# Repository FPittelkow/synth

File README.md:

# synth

The circuit is based on the [Totoro-Synth by SyntherJack](https://syntherjack.net/totoro-1-ic-simple-synth/)

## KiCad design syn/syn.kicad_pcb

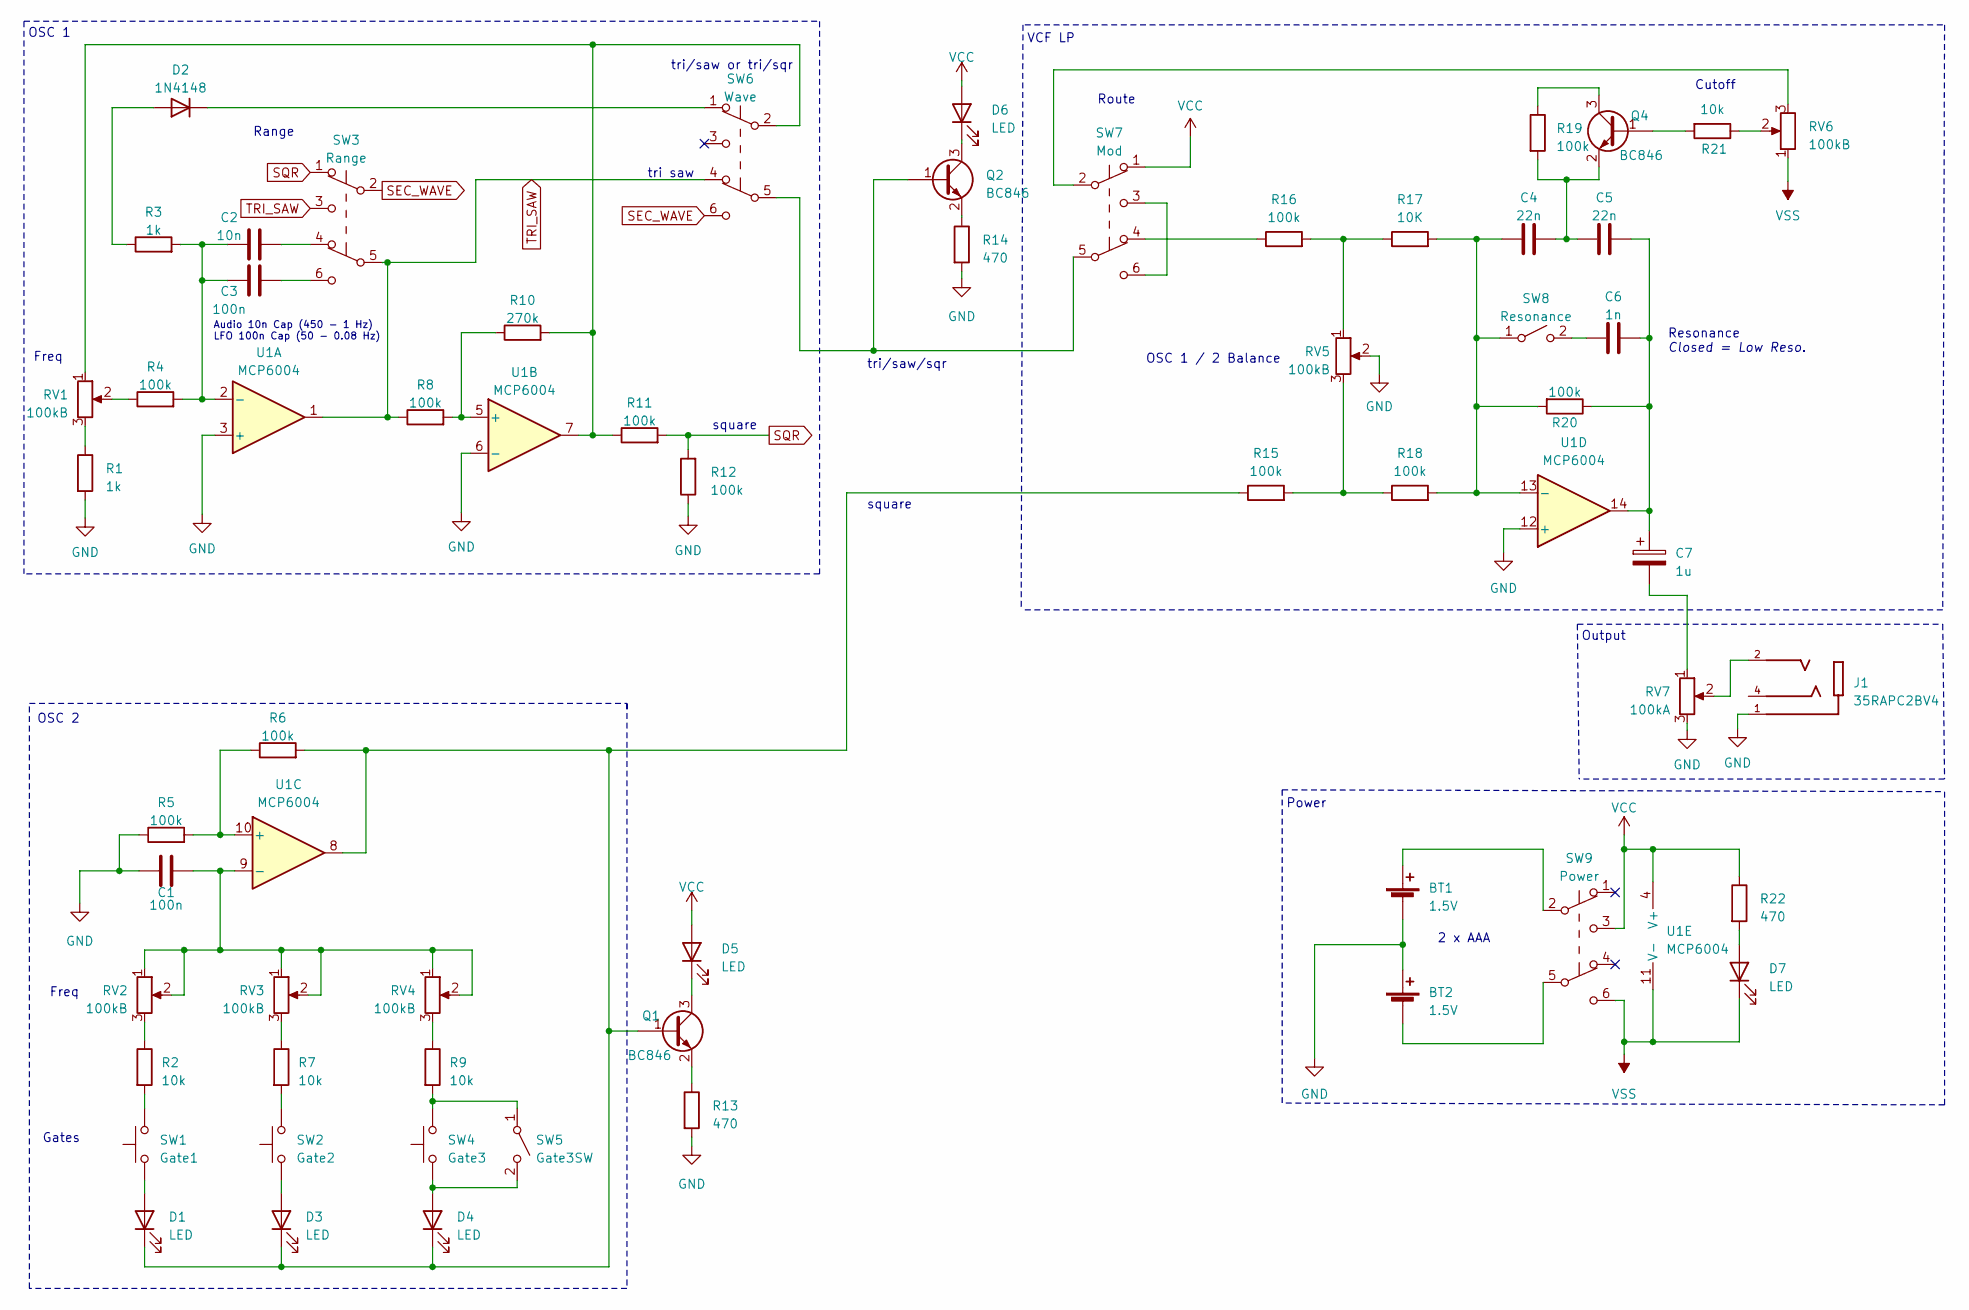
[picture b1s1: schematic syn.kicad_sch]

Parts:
BT1, BT2: 1.5V; BatteryHolder_Keystone_2466_1xAAA
C1, C3: 100n; C_0805_2012Metric_Pad1.18x1.45mm_HandSolder
C2: 10n; C_0805_2012Metric_Pad1.18x1.45mm_HandSolder
C4, C5: 22n; C_0805_2012Metric_Pad1.18x1.45mm_HandSolder
C6: 1n; C_0805_2012Metric_Pad1.18x1.45mm_HandSolder
C7: 1u; C_0805_2012Metric_Pad1.18x1.45mm_HandSolder
D1, D3, D4, D5, D6, D7: LED; LED_D3.0mm
D2: 1N4148; D_DO-35_SOD27_P7.62mm_Horizontal
J1: 35RAPC2BV4; SWITCHCRAFT_35RAPC2BV4; PARTREV G
Q1, Q2, Q4: BC846; SOT-23
R1, R3: 1k; R_0805_2012Metric_Pad1.20x1.40mm_HandSolder
R2, R7, R9, R21: 10k; R_0805_2012Metric_Pad1.20x1.40mm_HandSolder
R4, R5, R6, R8, R11, R12, R15, R16, R18, R19, R20: 100k; R_0805_2012Metric_Pad1.20x1.40mm_HandSolder
R10: 270k; R_0805_2012Metric_Pad1.20x1.40mm_HandSolder
R13, R14, R22: 470; R_0805_2012Metric_Pad1.20x1.40mm_HandSolder
R17: 10K; R_0805_2012Metric_Pad1.20x1.40mm_HandSolder
RV1, RV2, RV3, RV4, RV5, RV6: 100kB; Potentiometer_Bourns_PTV09A-1_Single_Vertical
RV7: 100kA; Potentiometer_Bourns_PTV09A-1_Single_Vertical
SW1: Gate1; SW_PUSH_6mm_H9.5mm
SW2: Gate2; SW_PUSH_6mm_H9.5mm
SW3: Range; SW_NKK_G1xJP
SW4: Gate3; SW_PUSH_6mm_H9.5mm
SW5: Gate3SW; SW_NKK_G1xJP
SW6: Wave; SW_NKK_G1xJP
SW7: Mod; SW_NKK_G1xJP
SW8: Resonance; SW_NKK_G1xJP
SW9: Power; SW_NKK_G1xJP
U1: MCP6004; DIP-14_W7.62mm

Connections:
GND: BT1.2 (-), BT2.1 (+), C1.1, J1.1, R1.2, R5.1, R12.1, R13.2, R14.2, RV5.2, RV7.3, U1.3 (+), U1.6 (-), U1.12 (+)
unnamed: BT1.1 (+), SW9.2 (B)
unnamed: BT2.2 (-), SW9.5 (B)
unnamed: C1.2, RV2.1, RV2.2, RV3.1, RV3.2, RV4.1, RV4.2, U1.9 (-)
unnamed: C2.1, C3.1, R3.2, R4.2, U1.2 (-)
unnamed: C2.2, SW3.4 (A)
unnamed: C3.2, SW3.6 (C)
unnamed: C4.1, R17.2, R18.2, R20.2, SW8.1 (A), U1.13 (-)
unnamed: C4.2, C5.1, Q4.2 (E), R19.2
unnamed: C5.2, C6.2, C7.1, R20.1, U1.14
unnamed: C6.1, SW8.2 (B)
unnamed: C7.2, RV7.1
unnamed: D1.1 (K), D3.1 (K), D4.1 (K), Q1.1 (B), R6.2, R15.1, U1.8
unnamed: D1.2 (A), SW1.1
unnamed: D2.1 (K), SW6.1 (A)
unnamed: D2.2 (A), R3.1
unnamed: D3.2 (A), SW2.1
unnamed: D4.2 (A), SW4.1, SW5.2 (B)
unnamed: D5.1 (K), Q1.3 (C)
unnamed: D6.1 (K), Q2.3 (C)
unnamed: D7.2 (A), R22.2
unnamed: J1.2, RV7.2
unnamed: Q1.2 (E), R13.1
unnamed: Q2.1 (B), SW6.5 (B), SW7.5 (B)
unnamed: Q2.2 (E), R14.1
unnamed: Q4.1 (B), R21.2
unnamed: Q4.3 (C), R19.1
unnamed: R1.1, RV1.3
unnamed: R2.1, RV2.3
unnamed: R2.2, SW1.2
unnamed: R4.1, RV1.2
unnamed: R5.2, R6.1, U1.10 (+)
unnamed: R7.1, RV3.3
unnamed: R7.2, SW2.2
unnamed: R9.1, RV4.3
unnamed: R9.2, SW4.2, SW5.1 (A)
unnamed: R8.2, R10.1, U1.5 (+)
unnamed: R10.2, R11.1, RV1.1, SW6.2 (B), U1.7
unnamed: R15.2, R18.1, RV5.3
unnamed: R16.1, SW7.4 (A)
unnamed: R16.2, R17.1, RV5.1
unnamed: R21.1, RV6.2
unnamed: RV6.3, SW7.2 (B)
unnamed: SW7.3 (C), SW7.6 (C)
SEC_WAVE: SW3.2 (B), SW6.6 (C)
SQR: R11.2, R12.2, SW3.1 (A)
TRI_SAW: R8.1, SW3.3 (C), SW3.5 (B), SW6.4 (A), U1.1
VCC: D5.2 (A), D6.2 (A), R22.1, SW7.1 (A), SW9.3 (C), U1.4 (V+)
VSS: D7.1 (K), RV6.1, SW9.6 (C), U1.11 (V-)

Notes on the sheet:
OSC 1
Freq
OSC 2
Gates
Audio 10n Cap (450 - 1 Hz) LFO 100n Cap (50 - 0.08 Hz)
Range
tri saw
tri/saw or tri/sqr
square
tri/saw/sqr
square
VCF LP
Route
OSC 1 / 2 Balance
Power
2 x AAA
Output
Resonance
Closed = Low Reso.
Cutoff

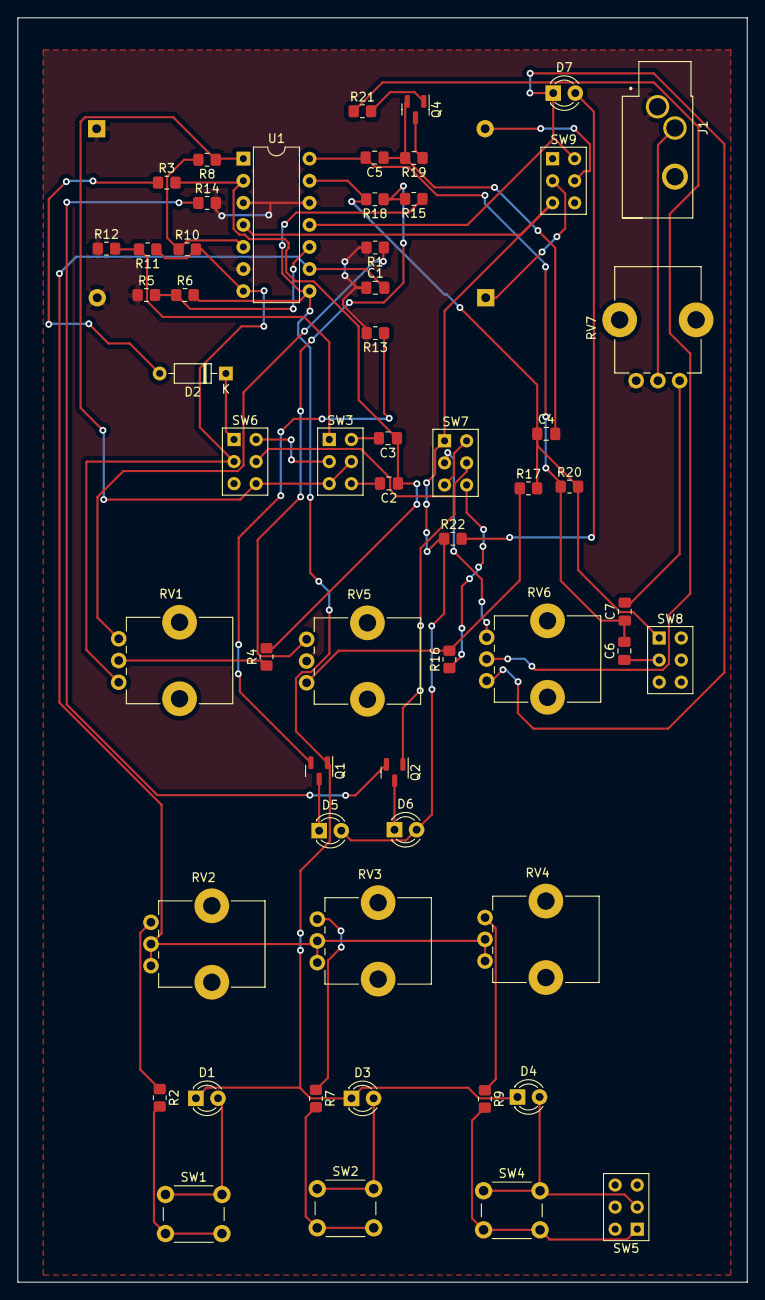
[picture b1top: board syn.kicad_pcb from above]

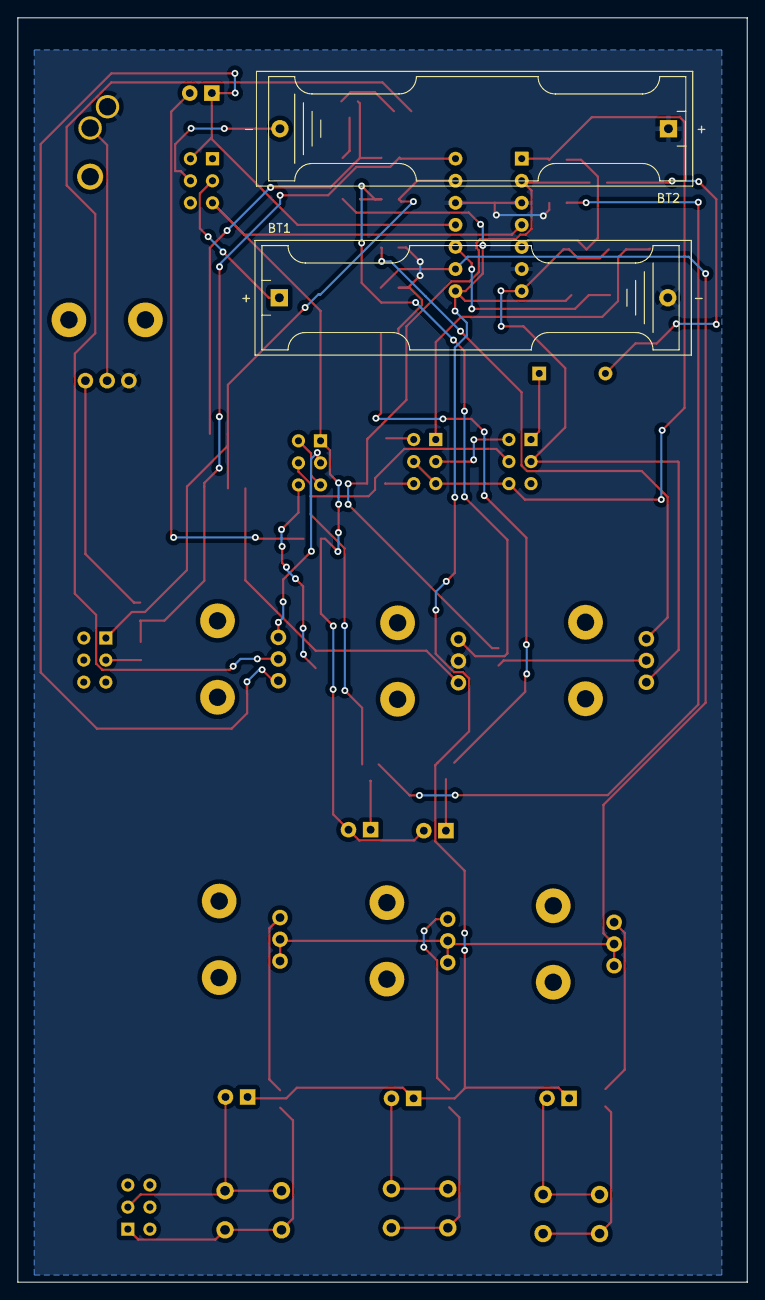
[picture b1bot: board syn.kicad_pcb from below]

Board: 2 copper layers, 83.9 x 145.5 mm, 59 parts (2 on the bottom side), 49 nets.

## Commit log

2021-06-09 init
2021-06-11 structure
2021-06-12 Readme
